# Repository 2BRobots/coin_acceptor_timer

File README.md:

# Coin Acceptor Timer module for Vending Machines

The timer must be powered with regulated 12 VDC. When there is electric power, the POWER LED will remain lit as the power present indicator and the STAT LED will light momentarily once. Whenever the timer is enabled, the RELAY LED will illuminate while the timer remains active. When a pulse is received from the coin acceptor, the STAT LED will flash rapidly for each pulse received (credit), the pulses are always counted regardless of the timer is active or not.

The pulse input from the coin acceptor in the timer is open collector type. Which means that the coin acceptor must send a low logic signal (GND) every time it sends a credit and in standby state it must be floating (no voltage). The pulses must have a minimum width of 10 ms and a separation of 5 ms between pulses.

The timer is programmed to disable the relay between each transaction, if you need it to be constantly enabled while it has enough credits please contact us for customization.

How to modify the settings:

1. To change the number of pulses (credits) with which the timer is activated press the UP and DOWN buttons. With UP it increases and with DOWN it decreases, each time the setting is changed the STAT LED will flash rapidly. When the upper or lower limit is reached, the STAT LED flash slowly.

2. To change the time (seconds) that the timer is enabled, the procedure is the same as the previous one, exept you must keep the TIME / RESET button pressed while pressing UP and DOWN.

3. To reset the timer to factory settings, press and hold the TIME / RESET button when the timer is turned on. The STAT LED will flash rapidly 2 times indicating that the restart was successful. Default values are 1 credit for 5 seconds.

Note: the maximum value for both cases (time and credits) is 100 and the minimum is 1.
The timer does not lose its settings when it is turned on and off.

You can purchase this module on Tindie: https://www.tindie.com/products/Danny024/timer-module-for-vending-machine/

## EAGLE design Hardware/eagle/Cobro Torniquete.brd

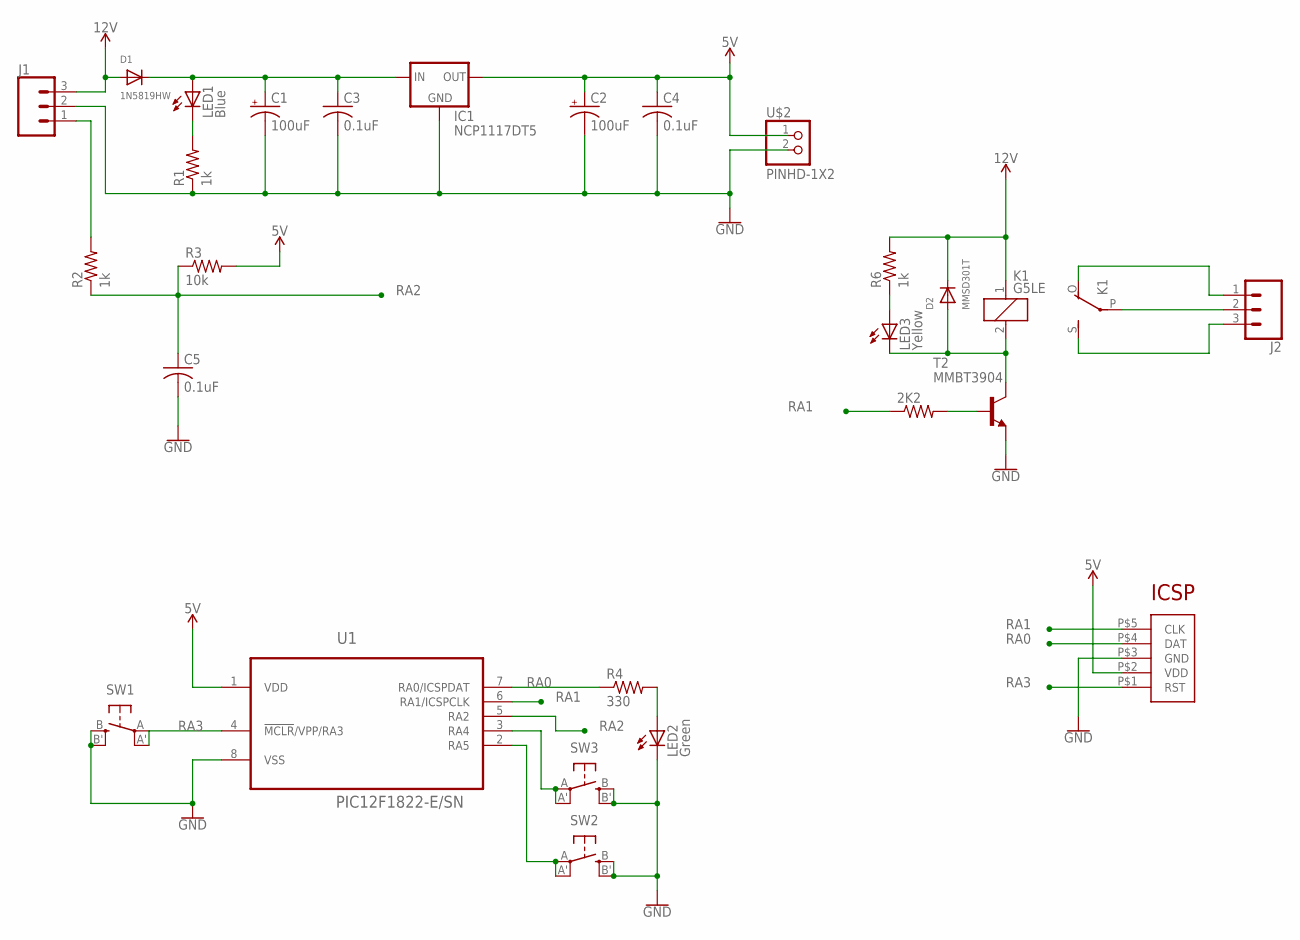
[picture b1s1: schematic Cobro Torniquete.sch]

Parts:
2K2: R-US_R0805; R0805
C1, C2: 100uF; 140CLH-0810
C3, C4, C5: 0.1uF; C0603K
D1: 1N5819HW; SOD-123
D2: MMSD301T; SOD-123
IC1: NCP1117DT5; TO252
J1, J2: CONN_03-SCREW-5MM; SCREWTERMINAL-5MM-3
K1: G5LE
LED1: Blue; CHIPLED_1206
LED2: Green; CHIPLED_1206
LED3: Yellow; CHIPLED_1206
R1, R2, R6: 1k; R0805
R3: 10k; R0805
R4: 330; R0805
SW1, SW2, SW3: SPST_TACT-EVQQ2; EVQ-Q2
T2: MMBT3904; SOT23-BEC
U1: PIC12F1822-E/SN; SOIC127P600X175-8N
U$1: ICSP_POGO
U$2: PINHD-1X2; 1X2

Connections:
5V: C2.+, C4.1, IC1.3 (OUT), R3.2, U1.1 (VDD), U$1.P$2 (VDD), U$2.1
12V: D1.A, D2.C, J1.3, K1.1, R6.2
GND: C1.-, C2.-, C3.2, C4.2, C5.2, IC1.1 (GND), J1.2, LED2.C, R1.1, SW1.B (S), SW1.B' (S1), SW2.B (S), SW2.B' (S1), SW3.B (S), SW3.B' (S1), T2.E, U1.8 (VSS), U$1.P$3 (GND), U$2.2
unnamed: C1.+, C3.1, D1.C, IC1.2 (IN), LED1.A
unnamed: LED1.C, R1.2
unnamed: J2.2, K1.P
unnamed: J1.1, R2.2
unnamed: J2.3, K1.S
unnamed: J2.1, K1.O
unnamed: D2.A, K1.2, LED3.C, T2.C
unnamed: LED2.A, R4.2
unnamed: LED3.A, R6.1
unnamed: 2K2.2, T2.B
unnamed: SW3.A, SW3.A' (P1), U1.3 (RA4)
unnamed: SW2.A, SW2.A' (P1), U1.2 (RA5)
RA0: R4.1, U1.7 (RA0/ICSPDAT), U$1.P$4 (DAT)
RA1: 2K2.1, U1.6 (RA1/ICSPCLK), U$1.P$5 (CLK)
RA2: C5.1, R2.1, R3.1, U1.5 (RA2)
RA3: SW1.A, SW1.A' (P1), U1.4 (!MCLR!/VPP/RA3), U$1.P$1 (RST)

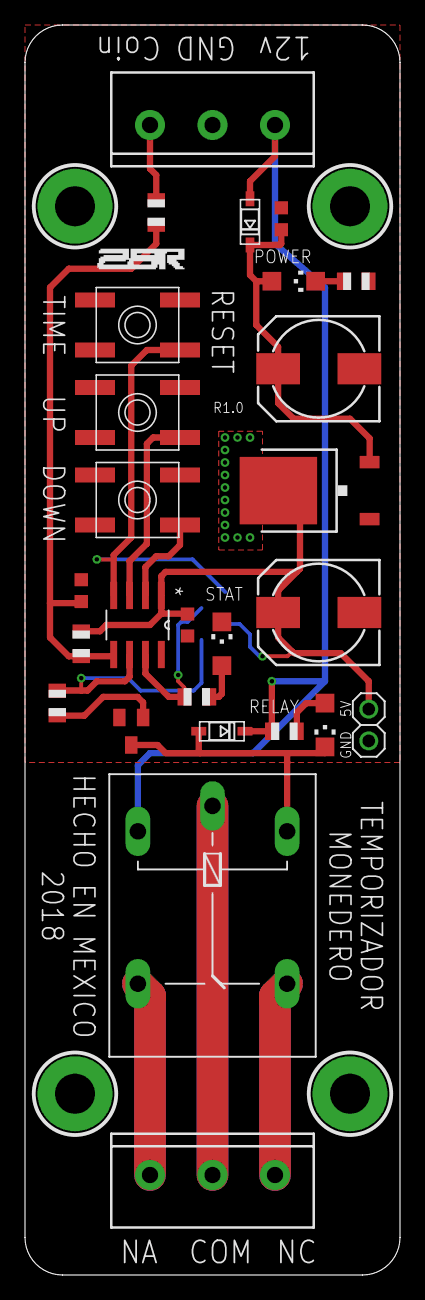
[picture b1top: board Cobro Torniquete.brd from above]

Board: 2 copper layers, 30.0 x 100.0 mm, 27 parts (1 on the bottom side), 19 nets.

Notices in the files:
parts and their libraries:
SparkFun-Connectors: Licensing: Creative Commons ShareAlike 4.0 International - https://creativecommons.org/licenses/by-sa/4.0
